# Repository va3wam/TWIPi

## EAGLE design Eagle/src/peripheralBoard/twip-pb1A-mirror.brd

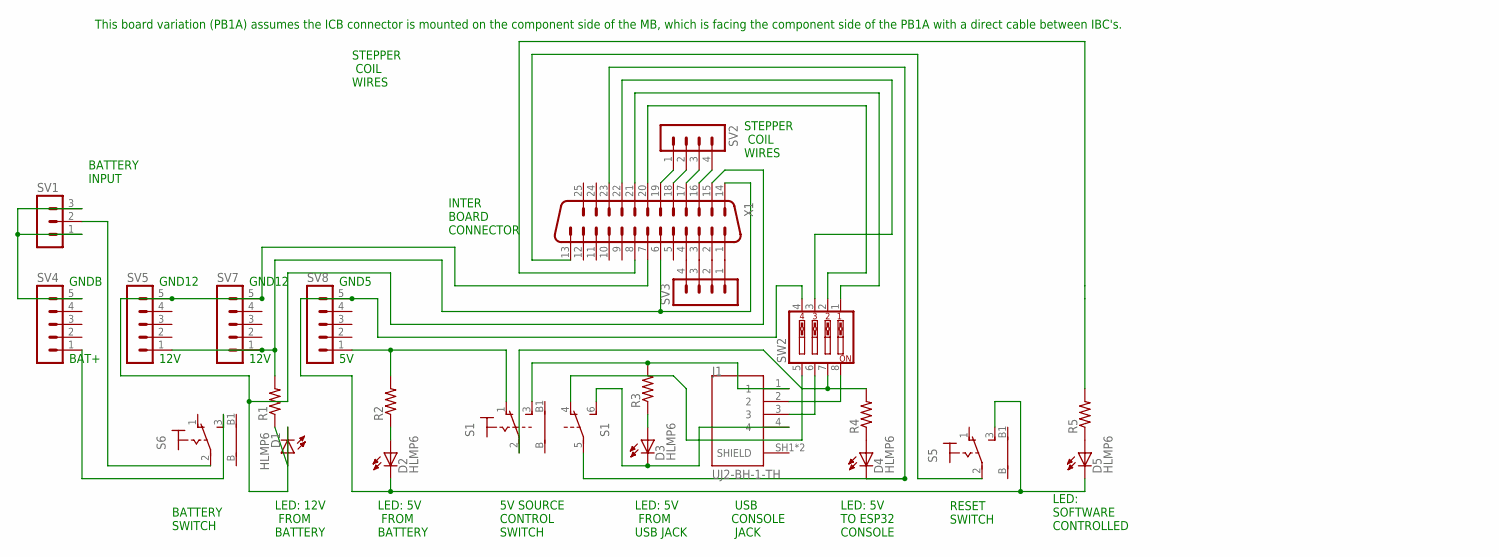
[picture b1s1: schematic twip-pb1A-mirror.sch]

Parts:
D1, D2, D3, D4, D5: HLMP6
J1: UJ2-BH-1-TH; CUI_UJ2-BH-1-TH
R1, R2, R3, R4, R5: R-US_0207/5V; 0207/5V
S1: 9070-2W
S5, S6: 9070-1W
SV1: MA03-1
SV2, SV3: MA04-1
SV4, SV5, SV7, SV8: MA05-1
SW2: SW_DIP-4; EDG-04
X1: M25VP

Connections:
unnamed: D1.A, R1.1
unnamed: D2.A, R2.1
unnamed: D3.A, R3.1
unnamed: D4.A, R4.1
unnamed: D5.A, R5.1
unnamed: SV1.1, SV1.3, SV4.5
unnamed: S6.2, SV1.2
unnamed: R1.2, SV5.1, SV7.1, X1.6, X1.14
unnamed: J1.1, R3.2, S1.3 (S)
unnamed: S6.3 (S), SV4.1
unnamed: SV2.1, X1.19
unnamed: R2.2, S1.1 (O), SV8.1
unnamed: J1.2, SW2.8
unnamed: SV3.4, X1.4
unnamed: SV3.3, X1.3
unnamed: SV3.2, X1.2
unnamed: SV3.1, X1.1
unnamed: SV2.2, X1.18
unnamed: SV2.3, X1.17
unnamed: SV2.4, X1.16
unnamed: R5.2, X1.8
unnamed: R4.2, S1.2, SW2.7
unnamed: D3.K, J1.4, S1.6 (S)
unnamed: SW2.1, X1.21
unnamed: SW2.3, X1.22
unnamed: SW2.2, X1.20
unnamed: D4.K, S1.5, X1.23
unnamed: S5.2, X1.13
unnamed: D1.K, SV5.5, SV7.5, X1.7, X1.15
unnamed: S1.4 (O), SW2.5
unnamed: D2.K, D5.K, S5.3 (S), SV8.5, SW2.4
unnamed: J1.3, SW2.6

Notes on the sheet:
BATTERY SWITCH
LED: 5V FROM BATTERY
LED: 12V FROM BATTERY
LED: 5V TO ESP32 CONSOLE
LED: SOFTWARE CONTROLLED
RESET SWITCH
5V SOURCE CONTROL SWITCH
LED: 5V FROM USB JACK
USB CONSOLE JACK
BATTERY INPUT
STEPPER COIL WIRES
INTER BOARD CONNECTOR
This board variation (PB1A) assumes the ICB connector is mounted on the component side of the MB, which is facing the component side of the PB1A with a direct cable between IBC's.
12V
BAT+
GNDB
GND12
GND5

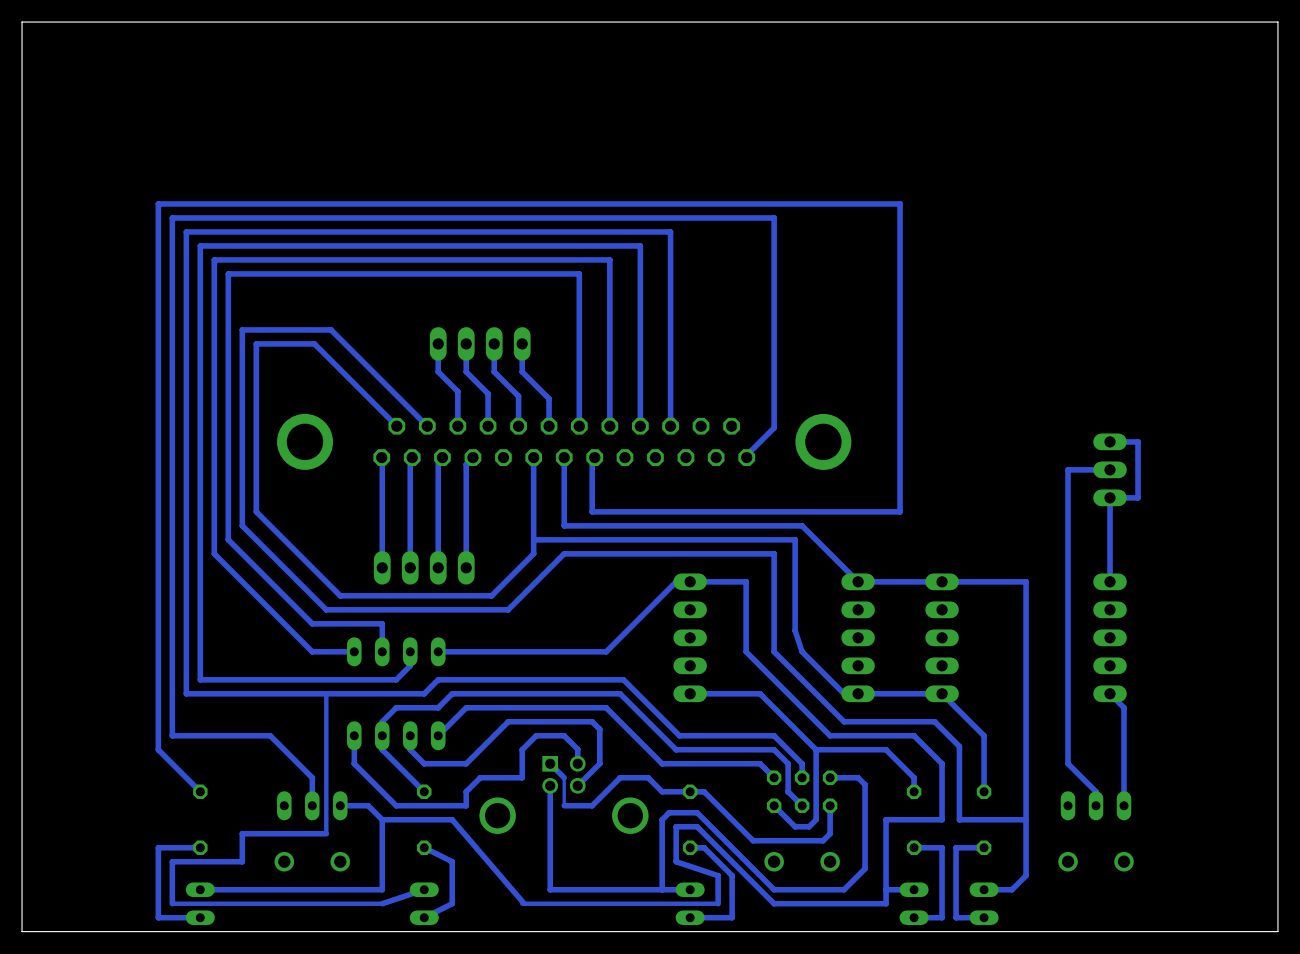
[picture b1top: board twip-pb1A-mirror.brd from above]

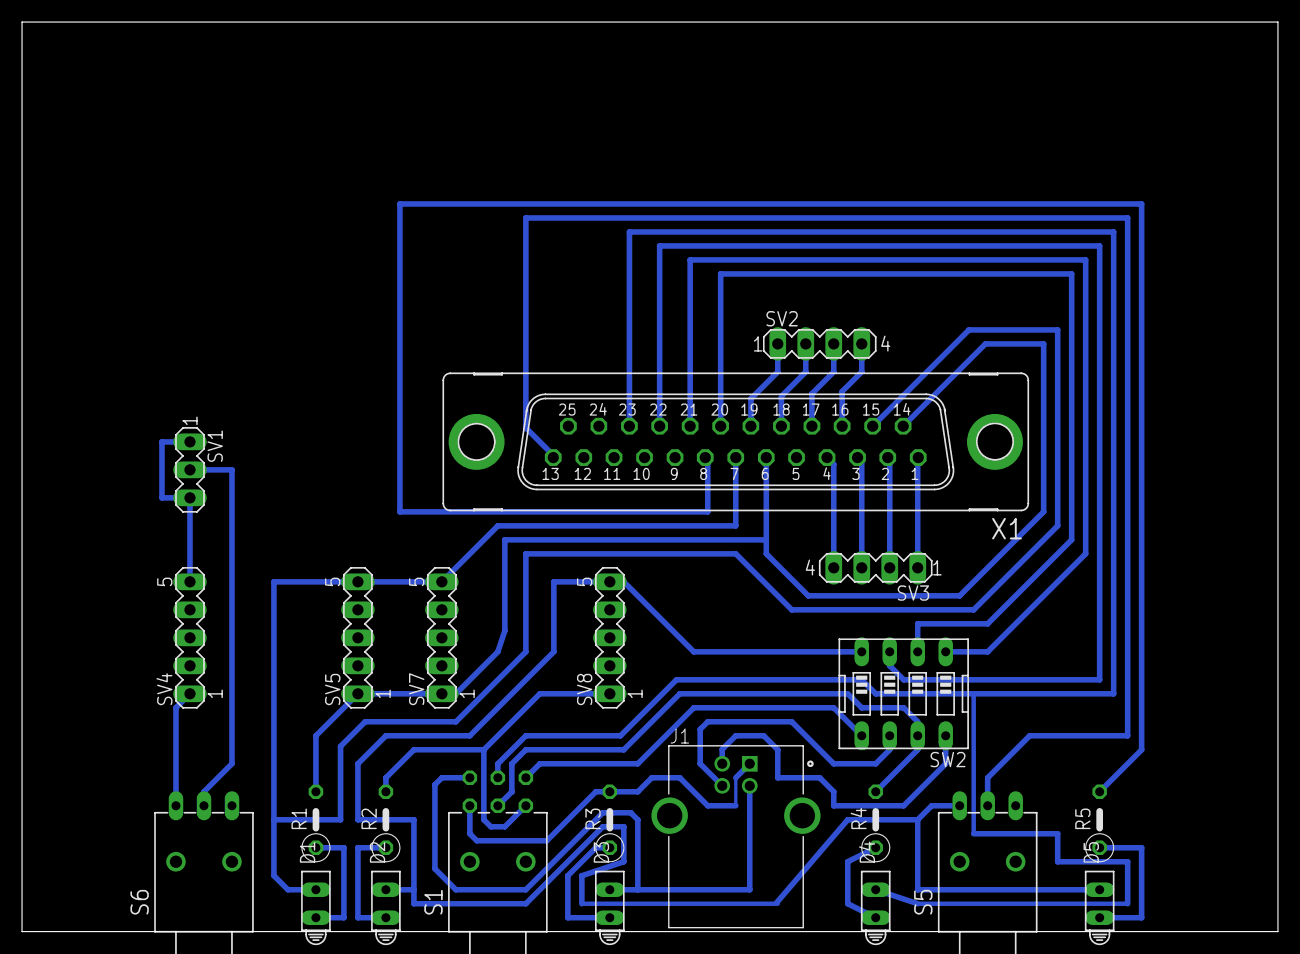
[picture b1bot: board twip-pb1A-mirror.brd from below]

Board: 2 copper layers, 114.0 x 82.5 mm, 23 parts (23 on the bottom side), 32 nets.

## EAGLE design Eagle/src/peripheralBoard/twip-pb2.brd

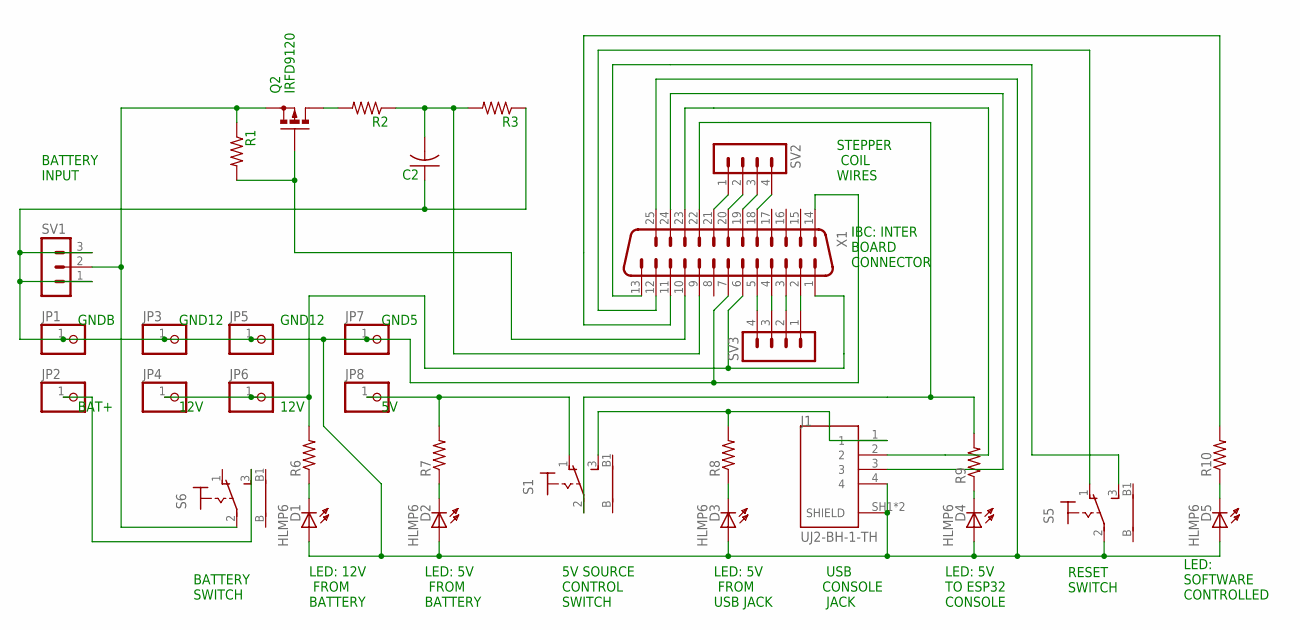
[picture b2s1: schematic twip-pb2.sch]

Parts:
C2: C-US050-025X075; C050-025X075
D1, D2, D3, D4, D5: HLMP6
J1: UJ2-BH-1-TH; CUI_UJ2-BH-1-TH
JP1, JP2, JP3, JP4, JP5, JP6, JP7, JP8: PINHD-1X1; 1X01
Q2: IRFD9120; C370-01
R1, R2, R3, R6, R7, R8, R9, R10: R-US_0207/10; 0207/10
S1, S5, S6: 9070-1W
SV1: MA03-1
SV2, SV3: MA04-1
X1: M25VP

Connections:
unnamed: D4.K, R9.1
unnamed: D1.K, R6.1
unnamed: D2.K, R7.1
unnamed: C2.1, D1.A, D2.A, D3.A, D4.A, D5.A, J1.4, J1.SH1 (SHIELD), J1.SH2 (SHIELD), JP1.1, JP3.1, JP5.1, JP7.1, R3.1, S5.2, SV1.1, SV1.3, X1.7, X1.14, X1.25
unnamed: D3.K, R8.1
unnamed: JP8.1, R7.2, S1.1 (O)
unnamed: Q2.S, R1.1, S6.2, SV1.2
unnamed: JP4.1, JP6.1, R6.2, X1.1, X1.6
unnamed: D5.K, R10.1
unnamed: JP2.1, S6.3 (S)
unnamed: SV2.1, X1.21
unnamed: S5.1 (O), X1.12
unnamed: J1.1, R8.2, S1.3 (S)
unnamed: SV3.1, X1.2
unnamed: SV3.2, X1.3
unnamed: SV3.3, X1.4
unnamed: SV3.4, X1.5
unnamed: SV2.2, X1.20
unnamed: SV2.3, X1.19
unnamed: SV2.4, X1.18
unnamed: R10.2, X1.11
unnamed: J1.2, X1.23
unnamed: J1.3, X1.24
unnamed: R9.2, S1.2, X1.22
unnamed: Q2.D, Q2.D1 (D), R2.2
unnamed: Q2.G, R1.2, X1.10
unnamed: S5.3 (S), X1.13
unnamed: C2.2, R2.1, R3.2, X1.9

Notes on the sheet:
BATTERY SWITCH
LED: 5V FROM BATTERY
LED: 12V FROM BATTERY
LED: 5V TO ESP32 CONSOLE
LED: SOFTWARE CONTROLLED
RESET SWITCH
5V SOURCE CONTROL SWITCH
LED: 5V FROM USB JACK
USB CONSOLE JACK
BATTERY INPUT
STEPPER COIL WIRES
IBC: INTER BOARD CONNECTOR
12V
BAT+
GNDB
GND12
GND5

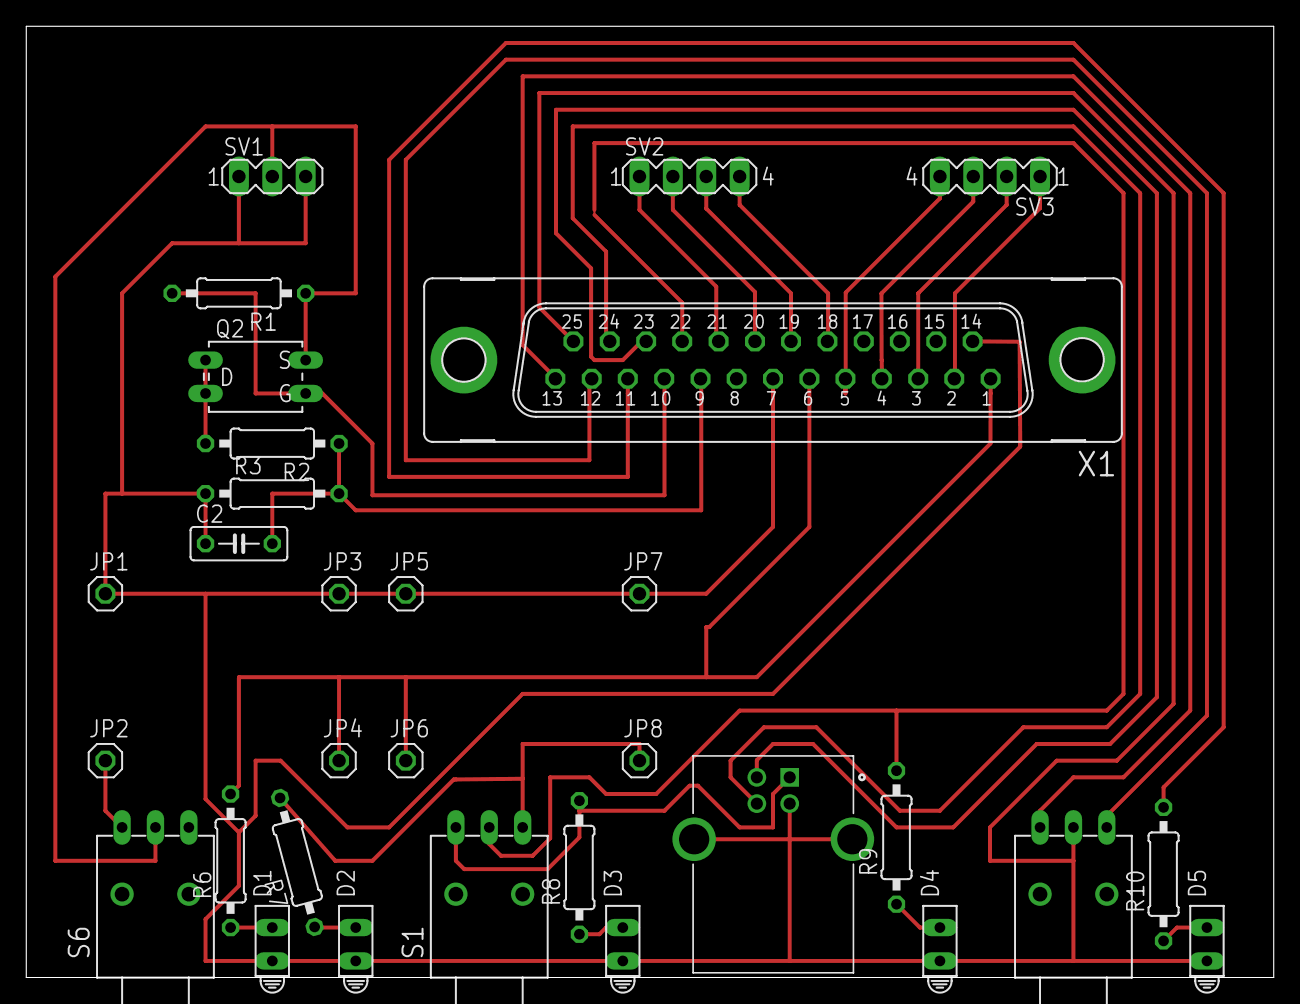
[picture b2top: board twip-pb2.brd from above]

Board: 2 copper layers, 94.9 x 72.4 mm, 31 parts (0 on the bottom side), 28 nets.

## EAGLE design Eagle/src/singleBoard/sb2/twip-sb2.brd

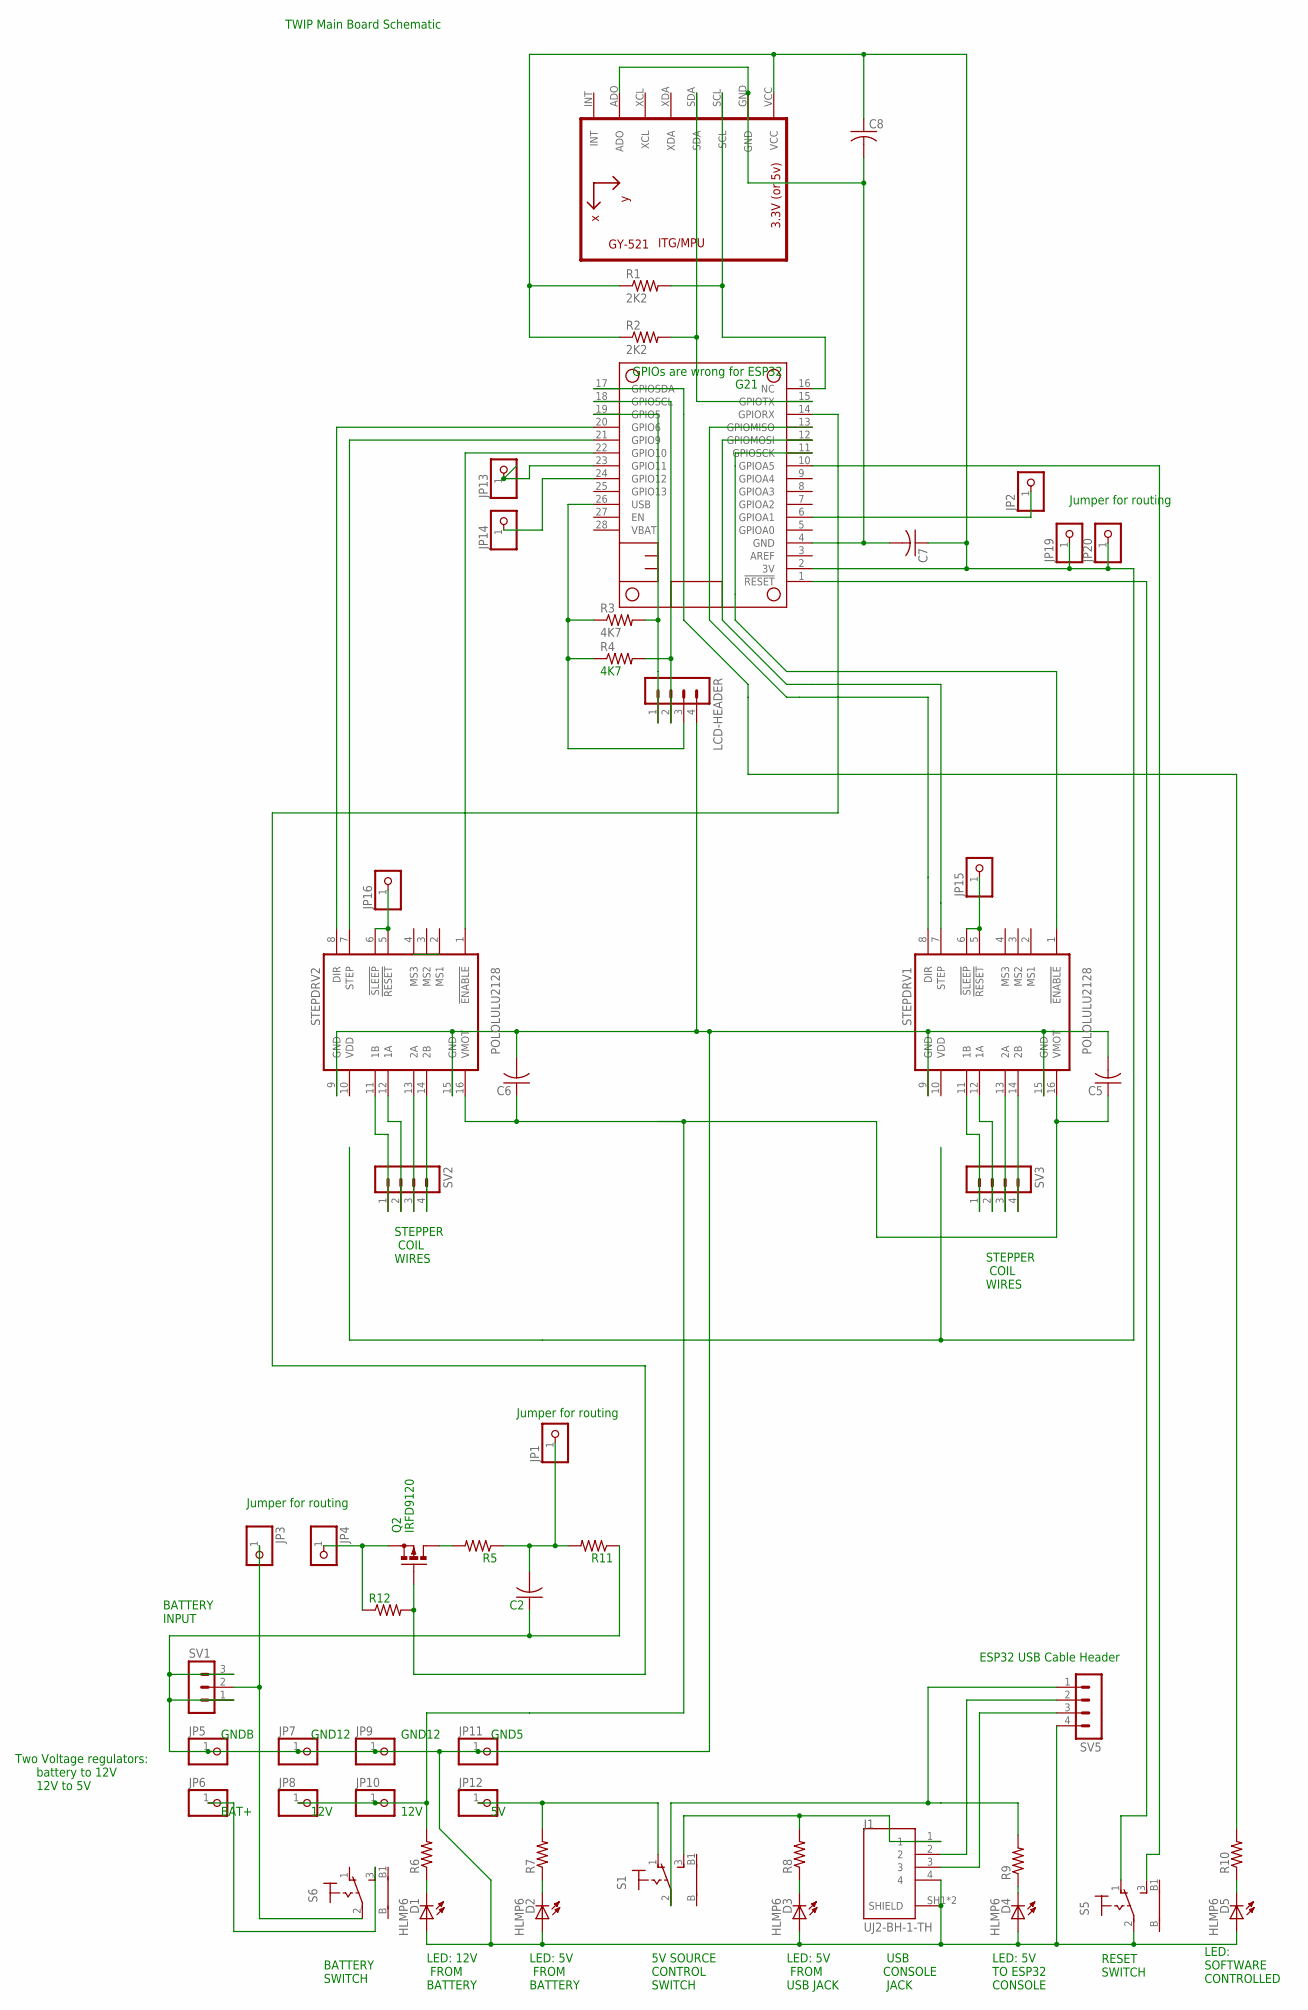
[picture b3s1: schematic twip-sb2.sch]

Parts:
C2: C-US050-025X075; C050-025X075
C5, C6, C7, C8: C-US050-024X044; C050-024X044
D1, D2, D3, D4, D5: HLMP6
J1: UJ2-BH-1-TH; CUI_UJ2-BH-1-TH
JP1, JP2, JP3, JP4, JP5, JP6, JP7, JP8, JP9, JP10, JP11, JP12, JP13, JP14, JP15, JP16, JP19, JP20: PINHD-1X1; 1X01
LCD-HEADER: MA04-1
MS2: FEATHERWING_NOHOLES
Q2: IRFD9120; C370-01
R1, R2: 2K2; 0309/12
R3, R4: 4K7; 0309/12
R5, R6, R7, R8, R9, R10, R11, R12: R-US_0207/10; 0207/10
S1, S5, S6: 9070-1W
STEPDRV1, STEPDRV2: POLOLULU2128
SV1: MA03-1
SV2, SV3, SV5: MA04-1
U1: GY-521MPU6050; GY-521

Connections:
3V: C7.1, C8.1, JP19.1, JP20.1, MS2.2 (3V), R1.1, R2.1, U1.VCC
unnamed: C7.2, C8.2, MS2.4 (GND), U1.ADO, U1.GND
unnamed: MS2.13 (GPIOMISO), STEPDRV1.8 (DIR)
unnamed: MS2.1 (!RESET), S5.1 (O)
unnamed: JP15.1, STEPDRV1.5 (!RESET), STEPDRV1.6 (!SLEEP)
unnamed: MS2.14 (GPIORX), Q2.G, R12.2
unnamed: JP16.1, STEPDRV2.5 (!RESET), STEPDRV2.6 (!SLEEP)
unnamed: STEPDRV2.14 (2B), SV2.4
unnamed: C2.1, C5.2, C6.2, D1.A, D2.A, D3.A, D4.A, D5.A, J1.4, J1.SH1 (SHIELD), J1.SH2 (SHIELD), JP5.1, JP7.1, JP9.1, JP11.1, LCD-HEADER.4, R11.1, S5.2, STEPDRV1.9 (GND), STEPDRV1.15 (GND), STEPDRV2.9 (GND), STEPDRV2.15 (GND), SV1.1, SV1.3, SV5.4
unnamed: LCD-HEADER.1, MS2.19 (GPIO5), R3.2
unnamed: STEPDRV2.13 (2A), SV2.3
unnamed: STEPDRV2.12 (1A), SV2.2
unnamed: STEPDRV2.11 (1B), SV2.1
unnamed: MS2.12 (GPIOMOSI), STEPDRV1.7 (STEP)
unnamed: STEPDRV1.14 (2B), SV3.4
unnamed: MS2.16 (NC), R1.2, U1.SCL
unnamed: STEPDRV1.13 (2A), SV3.3
unnamed: STEPDRV1.12 (1A), SV3.2
unnamed: STEPDRV1.11 (1B), SV3.1
unnamed: MS2.11 (GPIOSCK), STEPDRV1.1 (!ENABLE)
unnamed: J1.2, SV5.2
unnamed: J1.3, SV5.3
unnamed: JP4.1, Q2.S, R12.1
unnamed: MS2.15 (GPIOTX), R2.2, U1.SDA
unnamed: MS2.20 (GPIO6), STEPDRV2.8 (DIR)
unnamed: MS2.17 (GPIOSDA), R10.2
unnamed: MS2.21 (GPIO9), STEPDRV2.7 (STEP)
unnamed: C2.2, JP1.1, R5.1, R11.2
unnamed: MS2.10 (GPIOA5), S5.3 (S)
unnamed: JP3.1, S6.2, SV1.2
unnamed: JP2.1, MS2.6 (GPIOA1)
unnamed: MS2.22 (GPIO10), STEPDRV2.1 (!ENABLE)
unnamed: LCD-HEADER.2, MS2.18 (GPIOSCL), R4.2
unnamed: JP13.1, MS2.23 (GPIO11)
unnamed: JP14.1, MS2.24 (GPIO12)
unnamed: JP6.1, S6.3 (S)
unnamed: C5.1, C6.1, JP8.1, JP10.1, R6.2, STEPDRV1.16 (VMOT), STEPDRV2.16 (VMOT)
unnamed: JP12.1, R7.2, S1.1 (O)
unnamed: R9.2, S1.2, SV5.1
unnamed: Q2.D, Q2.D1 (D), R5.2
unnamed: D4.K, R9.1
unnamed: D1.K, R6.1
unnamed: D2.K, R7.1
unnamed: D3.K, R8.1
unnamed: J1.1, R8.2, S1.3 (S)
unnamed: D5.K, R10.1
USB: LCD-HEADER.3, MS2.26 (USB), R3.1, R4.1
VDD: STEPDRV1.10 (VDD), STEPDRV2.10 (VDD)

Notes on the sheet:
GPIOs are wrong for ESP32
G21
TWIP Main Board Schematic
BATTERY SWITCH
LED: 5V FROM BATTERY
LED: 12V FROM BATTERY
LED: 5V TO ESP32 CONSOLE
LED: SOFTWARE CONTROLLED
RESET SWITCH
5V SOURCE CONTROL SWITCH
LED: 5V FROM USB JACK
USB CONSOLE JACK
BATTERY INPUT
STEPPER COIL WIRES
12V
BAT+
GNDB
GND12
GND5
Jumper for routing
ESP32 USB Cable Header
Two Voltage regulators: battery to 12V 12V to 5V

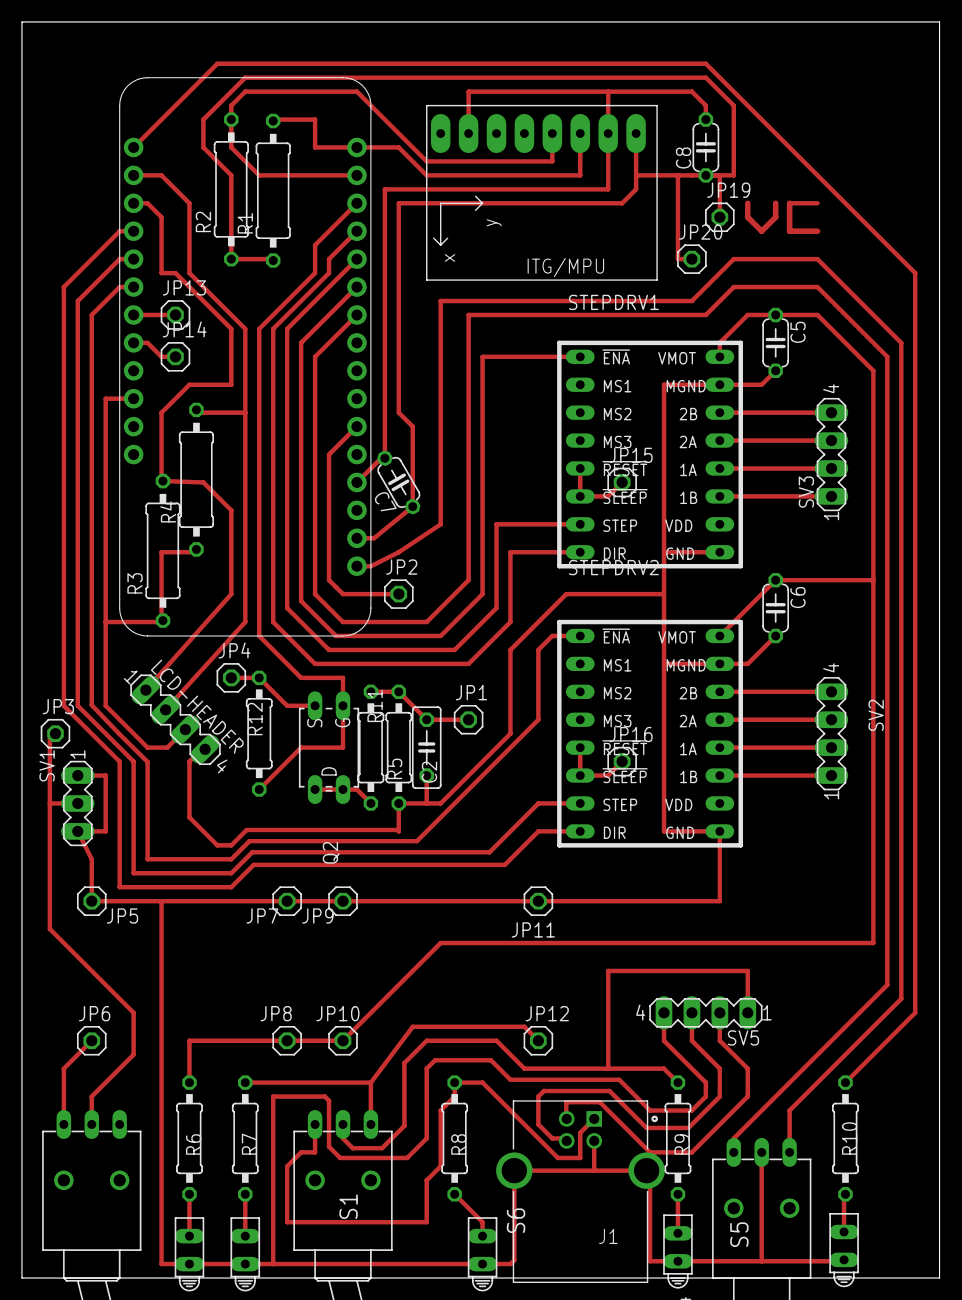
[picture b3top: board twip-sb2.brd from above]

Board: 2 copper layers, 83.5 x 114.3 mm, 54 parts (0 on the bottom side), 48 nets.

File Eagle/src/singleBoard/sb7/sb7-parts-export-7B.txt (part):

Partlist exported from C:/dae/GitHub/VA3WAM/TWIPi/Eagle/src/singleBoard/sb7/sb7pads.sch at 2020-01-23 9:33 PM

Part       Value               Device              Package             Description                                                                        ALLIED_NUMBER ALLIED_PRICE-STOCK                                              COMMENT   DESCRIPTION                                                                          DIGI-KEY_PART_NUMBER DIGI-KEY_PURCHASE_URL                                                                                                                                              EU_ROHS_COMPLIANCE HEIGHT MANUFACTURER_NAME MANUFACTURER_PART_NUMBER MF              MOUSER_PART_NUMBER MOUSER_PRICE-STOCK                                                  MP        MPN OC_FARNELL OC_NEWARK PACKAGE RS_PART_NUMBER RS_PRICE-STOCK SPICEPREFIX TE_PURCHASE_URL                                                                                                                                                              
BO-20VG                        PINHD-1X1           1X01                PIN HEADER                                                                                                                                                                                                                                                                                                                                                                                                                                                                                                                                                                                                                                                                                                                                                                                                                                                                                            
BO-20VP                        PINHD-1X1           1X01                PIN HEADER                                                                                                                                                                                                                                                                                                                                                                                                                                                                                                                                                                                                                                                                                                                                                                                                                                                                                            
C2         100nF               C-US050-025X075     C050-025X075        CAPACITOR, American symbol                                                                                                                                                                                                                                                                                                                                                                                                                                                                                                                                                                                                                                                                                   C                                                                                                                                                                                        
C5         100uF               C-US050-024X044     C050-024X044        CAPACITOR, American symbol                                                                                                                                                                                                                                                                                                                                                                                                                                                                                                                                                                                                                                                                                   C                                                                                                                                                                                        
C6         100uF               C-US050-024X044     C050-024X044        CAPACITOR, American symbol                                                                                                                                                                                                                                                                                                                                                                                                                                                                                                                                                                                                                                                                                   C                                                                                                                                                                                        
C7         .1uF                C-US050-024X044     C050-024X044        CAPACITOR, American symbol                                                                                                                                                                                                                                                                                                                                                                                                                                                                                                                                                                                                                                                                                   C                                                                                                                                                                                        
C8         .1uF                C-US050-024X044     C050-024X044        CAPACITOR, American symbol                                                                                                                                                                                                                                                                                                                                                                                                                                                                                                                                                                                                                                                                                   C                                                                                                                                                                                        
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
